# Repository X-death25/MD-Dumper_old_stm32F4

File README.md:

# MD-Dumper

What is it ?
-----

MD Dumper is an USB Sega Megadrive cartridge Dumper : <br>
Hardware is based on STM32F4 (BluePillV2) : STM32F4x1 MiniF4 https://github.com/WeActTC/MiniSTM32F4x1  <br>
New version also add some developpement feature witch can be usefull for Megadrive developper.  <br>

Feature :
-----

Firmware Version : 2.0

Software Version : 2.0

| Feature | Implemented |
| ------- | ----------- |
| ROM Dump up to 16 MEG  Classic              | :white_check_mark: |
| ROM Dump up to 32 MEG  Bankswitch           | :white_check_mark: |
| SRAM Backup Memory Classic                  | :white_check_mark: |
| SRAM Backup Memory Bankswitch               | :white_check_mark: |
| Rewrite Krikzz flashkit cart or compatible  | :white_check_mark: |

How to use it ?
-----

You just need an USB-C to USB. <br>
Connect the dumper to the PC and wait blue led activation. Insert game cartridge.  <br>
Start the software. Enjoy ! <br>

Operating System Compatibility
-----

Microsoft Windows 10

Where i can buy it ?
-----

https://www.tindie.com/products/xdeath/md-dumper-usb-megadrive-cartridge-readerwriter/

Linked Repositories
-----

My other projects related to Megadrive Hardware/Software developpement

-=Python MD-Dumper GUI=-
Easy and multiplateform GUI for MD-Dumper <br>
https://github.com/X-death25/PyMD-Dumper

-=DMC Direct Megadrive Connection=-
SGDK lib for bi-directionnal communication between Megadrive and PC <br>
*Coming Soon*

-=SMD_01=-
Simple 5V TTL 8MB Rewritable cartridge for testing code on real hardware <br>
*Coming Soon*

-=X-Flash=-
Altera EPM240 CPLD based Megadrive cartridge used for advanced research <br>
https://github.com/X-death25/X-Flash

Need Help ?
-----
If you need help or want to improvite or report a bug youre welcome to the official MD Dumper Discord !
https://discord.gg/8AtuA29Dnw

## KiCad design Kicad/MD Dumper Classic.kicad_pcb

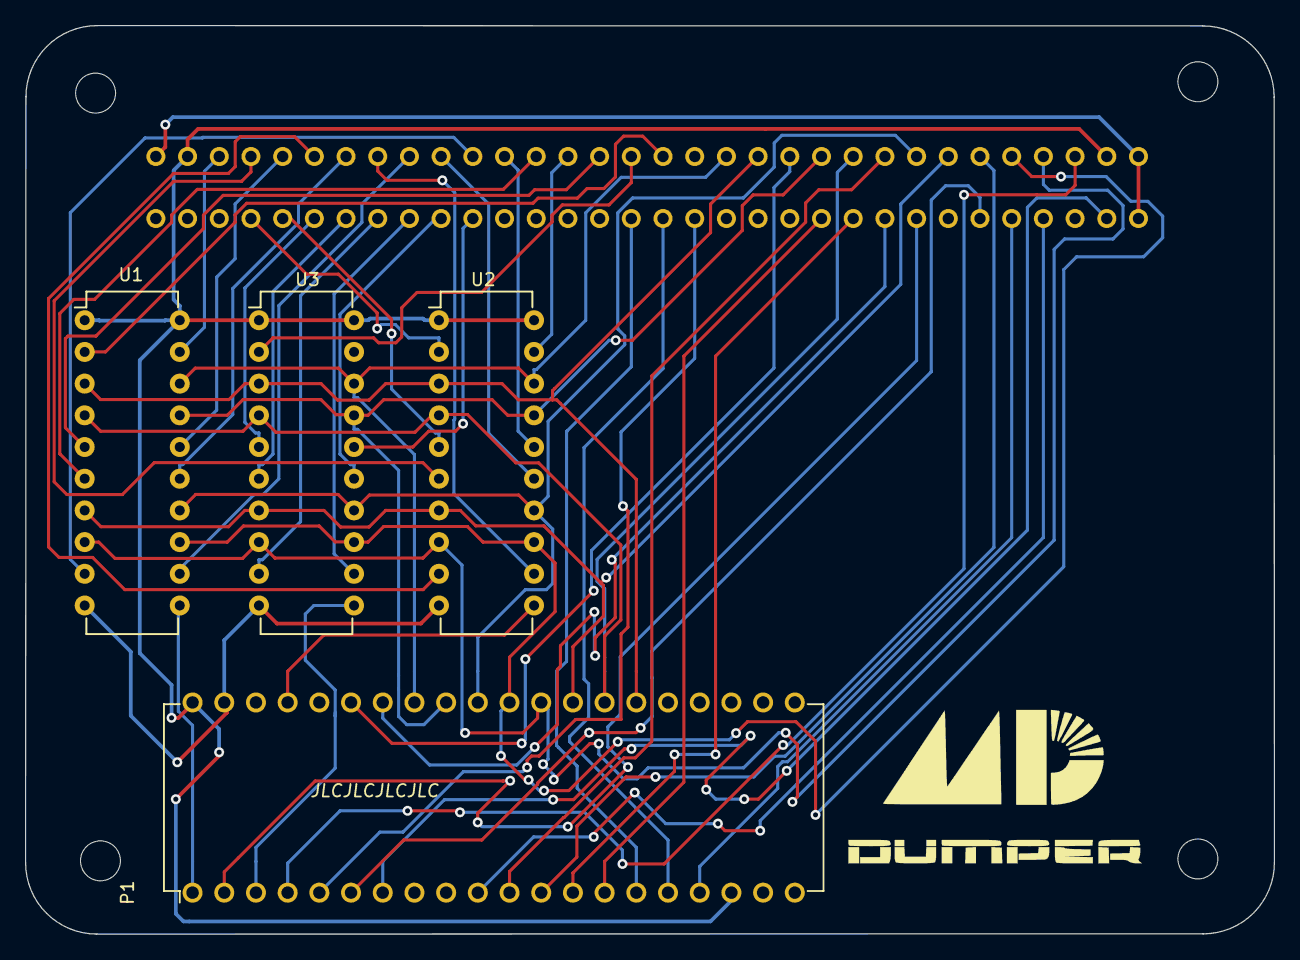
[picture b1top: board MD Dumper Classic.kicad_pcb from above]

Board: 2 copper layers, 100.1 x 72.8 mm, 11 parts (0 on the bottom side), 51 nets.

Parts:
Classic 12/2020: MD_Connector_H; MD_Slot
G1: LOGO; logo1
G2: LOGO; logo2
M1, M2, M3, M4: MountingHole_3.2mm_M3
P1: DIL40; STM32
U1, U2, U3: 74LS273; DIP-20_W7.62mm

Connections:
A0: Classic 12/2020.A17 (A0), U1.2 (Q0)
A1: Classic 12/2020.A15 (A1), U1.5 (Q1)
A2: Classic 12/2020.A13 (A2), U1.6 (Q2)
A3: Classic 12/2020.A11 (A3), U1.9 (Q3)
A4: Classic 12/2020.A09 (A4), U1.12 (Q4)
A5: Classic 12/2020.A07 (A5), U1.15 (Q5)
A6: Classic 12/2020.A05 (A6), U1.16 (Q6)
A7: Classic 12/2020.A03 (A7), U1.19 (Q7)
A8: Classic 12/2020.B04 (A8), U2.2 (Q0)
A9: Classic 12/2020.B05 (A9), U2.5 (Q1)
A10: Classic 12/2020.A04 (A10), U2.6 (Q2)
A11: Classic 12/2020.A06 (A11), U2.9 (Q3)
A12: Classic 12/2020.A08 (A12), U2.12 (Q4)
A13: Classic 12/2020.A10 (A13), U2.15 (Q5)
A14: Classic 12/2020.A12 (A14), U2.16 (Q6)
A15: Classic 12/2020.A14 (A15), U2.19 (Q7)
A16: Classic 12/2020.A16, U3.2 (Q0)
A17: Classic 12/2020.B06 (A17), U3.5 (Q1)
A18: Classic 12/2020.B07 (A18), U3.6 (Q2)
A19: Classic 12/2020.B08 (A19), U3.9 (Q3)
A20: Classic 12/2020.B09 (A20), U3.12 (Q4)
A21: Classic 12/2020.B10 (A21), U3.15 (Q5)
A22: Classic 12/2020.B11 (A22), U3.16 (Q6)
Clk1: P1.1, U1.11 (Cp)
Clk2: P1.37, U2.11 (Cp)
Clk3: P1.3, U3.11 (Cp)
D0_V: Classic 12/2020.A20 (D0), P1.26, U1.3 (D0), U2.3 (D0), U3.3 (D0)
D1_V: Classic 12/2020.A23 (D1), P1.27, U1.4 (D1), U2.4 (D1), U3.4 (D1)
D2_V: Classic 12/2020.A26 (D2), U1.7 (D2), U2.7 (D2), U3.7 (D2)
D4_V: Classic 12/2020.A28 (D4), P1.30, U1.13 (D4), U2.13 (D4), U3.13 (D4)
D5_V: Classic 12/2020.A25 (D5), P1.31, U1.14 (D5), U2.14 (D5), U3.14 (D5)
D6_V: Classic 12/2020.A22 (D6), P1.32, U1.17 (D6), U2.17 (D6), U3.17 (D6)
D7_V: Classic 12/2020.A19 (D7), P1.33, U1.18 (D7), U2.18 (D7), U3.18 (D7)
D8: Classic 12/2020.A21 (D8), P1.35
D9: Classic 12/2020.A24 (D9), P1.11
D10: Classic 12/2020.A27 (D10), P1.12
D11: Classic 12/2020.A30 (D11), P1.4
D12: Classic 12/2020.B25 (D12), P1.2
D13: Classic 12/2020.B24 (D13), P1.34
D14: Classic 12/2020.B23 (D14), P1.13
D15: Classic 12/2020.B22 (D15), P1.14
GND: Classic 12/2020.A01 (GND), Classic 12/2020.A18 (GND), Classic 12/2020.A32 (GND), Classic 12/2020.B32 (~CART), P1.19, P1.39, U1.10 (GND), U2.10 (GND), U3.10 (GND)
MD_AS: Classic 12/2020.B18 (AS), P1.5
MD_CE: Classic 12/2020.B17 (~CE), P1.16
MD_OE: Classic 12/2020.B16 (~OE), P1.15
MD_Rst: Classic 12/2020.B27 (~ROM_RST), P1.6
MD_TIME: Classic 12/2020.B31 (~TIME), P1.7
MD_UWR: Classic 12/2020.B29 (~Up_WR), P1.10
MD_WE: Classic 12/2020.B28 (~Low_WR), P1.17
VCC5: Classic 12/2020.A02 (VCC), Classic 12/2020.A31 (VCC), P1.18, P1.40, U1.1 (Mr), U1.20 (VCC), U2.1 (Mr), U2.20 (VCC), U3.1 (Mr), U3.20 (VCC)
d3_v: Classic 12/2020.A29 (D3), U1.8 (D3), U2.8 (D3), U3.8 (D3)

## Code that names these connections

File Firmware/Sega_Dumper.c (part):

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#define D15 GPIO6   //   PB6 ok 

//#define CLK_CLEAR 	GPIO0    // PB0 ok
#define CLK1 		GPIO12   // PB12 ok
#define CLK2 		GPIO10   // PB10 ok
#define CLK3 		GPIO14   // PB14 ok

#define OE 			GPIO7  // PB7 ok 
#define CE 			GPIO8  // PB8 ok
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    gpio_clear(GPIOB,OE);
    gpio_clear(GPIOB,CE);

    gpio_mode_setup(GPIOB,GPIO_MODE_OUTPUT, GPIO_PUPD_NONE,CLK1 | CLK2 | CLK3 );
    gpio_set_output_options(GPIOB,GPIO_OTYPE_PP,GPIO_OSPEED_50MHZ,CLK1 | CLK2 | CLK3 );
    gpio_clear(GPIOB,CLK1);
    gpio_clear(GPIOB,CLK2);
    gpio_clear(GPIOB,CLK3);

    gpio_mode_setup(GPIOC,GPIO_MODE_OUTPUT, GPIO_PUPD_NONE, LED_PIN);

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    setDataOutput();

    DirectWrite8(adr&0xFF);
    gpio_clear(GPIOB,CLK1);
    gpio_set(GPIOB,CLK1);

    DirectWrite8((adr>>8)&0xFF);
    gpio_clear(GPIOB,CLK2);
    gpio_set(GPIOB,CLK2);

    DirectWrite8((adr>>16)&0xFF);
    gpio_clear(GPIOB,CLK3);
    gpio_set(GPIOB,CLK3);

}

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    GPIO_MODER(GPIOB) = gpioreg_outputB;*/

    /*	GPIOB_BSRR |= CE;
    	GPIOB_BSRR |= CLK1;
    	GPIOB_BSRR |= CLK2;
    	GPIOB_BSRR |= CLK3;
    	GPIOB_BSRR |= OE;*/

    gpio_set(GPIOB,CE);
	gpio_set(GPIOA,ASTRB);
	gpio_set(GPIOA,UWR);
    gpio_set(GPIOB,CLK1);
    gpio_set(GPIOB,CLK2);
    gpio_set(GPIOB,CLK3);
    gpio_set(GPIOB,OE);
	gpio_set(GPIOA,TIME);

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        GPIO_MODER(GPIOB) = gpioreg_outputB;

        DirectWrite8((address+adr16)&0xFF);
        gpio_clear(GPIOB,CLK1);
        gpio_set(GPIOB,CLK1);

        DirectWrite8(((address+adr16)>>8)&0xFF);
        gpio_clear(GPIOB,CLK2);
        gpio_set(GPIOB,CLK2);

        DirectWrite8(((address+adr16)>>16)&0xFF);
        gpio_clear(GPIOB,CLK3);
        gpio_set(GPIOB,CLK3);*/

		setDataInput();
       /* GPIO_MODER(GPIOA) = gpioreg_inputA;
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
    setDataOutput();

    /* GPIOA_BSRR |= CE | CLK1| CLK2 | CLK3 | WE_FLASH | (CLK_CLEAR<<16);
     GPIOB_BSRR |= OE;*/

    gpio_set(GPIOB,CE);
    gpio_set(GPIOB,CLK1);
    gpio_set(GPIOB,CLK2);
    gpio_set(GPIOB,CLK3);
    gpio_set(GPIOB,OE);
    gpio_set(GPIOB,WE);

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    setDataOutput();

    gpio_set(GPIOB,CE);
    gpio_set(GPIOB,CLK1);
    gpio_set(GPIOB,CLK2);
    gpio_set(GPIOB,CLK3);
    gpio_set(GPIOB,OE);
    gpio_set(GPIOB,WE);

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    setDataOutput();

    gpio_set(GPIOB,CE);
    gpio_set(GPIOB,CLK1);
    gpio_set(GPIOB,CLK2);
    gpio_set(GPIOB,CLK3);
    gpio_set(GPIOB,OE);
    gpio_set(GPIOB,WE);

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    setDataOutput();

    gpio_set(GPIOB,CE);
    gpio_set(GPIOB,CLK1);
    gpio_set(GPIOB,CLK2);
    gpio_set(GPIOB,CLK3);
    gpio_set(GPIOB,OE);
    gpio_set(GPIOB,WE);

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    setDataOutput();

    gpio_set(GPIOB,CE);
    gpio_set(GPIOB,CLK1);
    gpio_set(GPIOB,CLK2);
    gpio_set(GPIOB,CLK3);
    gpio_set(GPIOB,OE);
    gpio_set(GPIOB,WE);

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    setDataOutput();

    gpio_set(GPIOB,CE);
    gpio_set(GPIOB,CLK1);
    gpio_set(GPIOB,CLK2);
    gpio_set(GPIOB,CLK3);
    gpio_set(GPIOB,OE);
    gpio_set(GPIOB,WE);

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    setDataOutput();

    gpio_set(GPIOB,CE);
    gpio_set(GPIOB,CLK1);
    gpio_set(GPIOB,CLK2);
    gpio_set(GPIOB,CLK3);
    gpio_set(GPIOB,OE);
    gpio_set(GPIOB,WE);

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
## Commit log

2022-03-20 Add User Manual
    updated User Manual
2022-03-27 Add USB Tools
2022-04-02 Add some EEPROM docs info
    Add some EEPROM docs info
2022-04-08 Add a No header software
    Can be usefull for non standard cartridge like Homebrew or UNL
2022-04-16 Update README.md
    Add a discord server
2022-04-21 Add files via upload
    Fix Master System game detecttion
2023-04-10 Release public version
2023-04-10 Release Schematics to public version
2023-04-10 Add gerber to public version
2023-04-10 Release Kicad PCB File to public version
2023-10-27 Add files via upload
    Add V2 Software
2023-10-27 Add files via upload
    Add V2 software Zip file
2024-07-05 V3
    -Add csv files for editable mapper of special games and flash chip
2024-09-03 Add files via upload
    Special thanks to Marv17 for french translation
